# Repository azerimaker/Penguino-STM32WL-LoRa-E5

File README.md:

## Penguino-STM32WL-LoRa-E5
 Seeedstudio's [LoRa-E5 STM32WLE5JC](https://www.seeedstudio.com/LoRa-E5-Wireless-Module-p-4745.html) module was recently announced, and I took the liberty of designing a Penguino Feather breakout board for it. Hopefully OSHW community would benfit from it. 

## About the Penguino Feather breakout
Managed to fit everything on a +2 layer (H1.6mm) low-cost PCB. Careful design choices allowed to have a good GND plane on the back to to achieve good (theoretical) RF performance. 

_Current version: 0.1_

Board requirements are standard: 
- 6mil traces/clearance
- 0.3mm drill

### Specs (SoC): 
- [STM32WLE5JC](https://www.st.com/en/microcontrollers-microprocessors/stm32wle5jc.html) Wireless SoC
- ARM Cortex M4 ultra-low-power MCU
- Integrated SX1262 RF transciever
- Frequency range: 150 MHz to 960 MHz.
- Modulation: LoRa®, (G)FSK, (G)MSK and BPSK
- Transmitter power: programmable up to +22 dBm 

### Specs ([LoRa-E5 module](](https://www.seeedstudio.com/LoRa-E5-Wireless-Module-p-4745.html))): 
- Frequency range: EU868/US915/AU915/AS923/KR920/IN865 (high-band design). FCC and CE Certified
- Ultra-low Power Consumption: as low as 2.1uA sleep current (WOR mode)
- High Performance: TXOP=22dBm@868/915MHz; -136.5dBm sensitivity for SF12 with 125KHz BW 
- Long Distance Use: 158dB link budget
- Size: 12mm * 12mm * 2.5mm 28 pins SMT
- For further specs plese see the respective product pages. 

### License:
- Hardware license: CERN-OHL-S v2
- Software license: under MIT unless otherise indicated 
- Documentation license:  CC BY-SA 4.0 International.

## Open Source Hardware
This board is an OSHWA approved design: [AZ000003](https://certification.oshwa.org/az000003.html)

### Contact:
If you have any question or comments please feel free to open an issue (or a discussion or drop me a message at [@azerimaker](https://twitter.com/azerimaker).

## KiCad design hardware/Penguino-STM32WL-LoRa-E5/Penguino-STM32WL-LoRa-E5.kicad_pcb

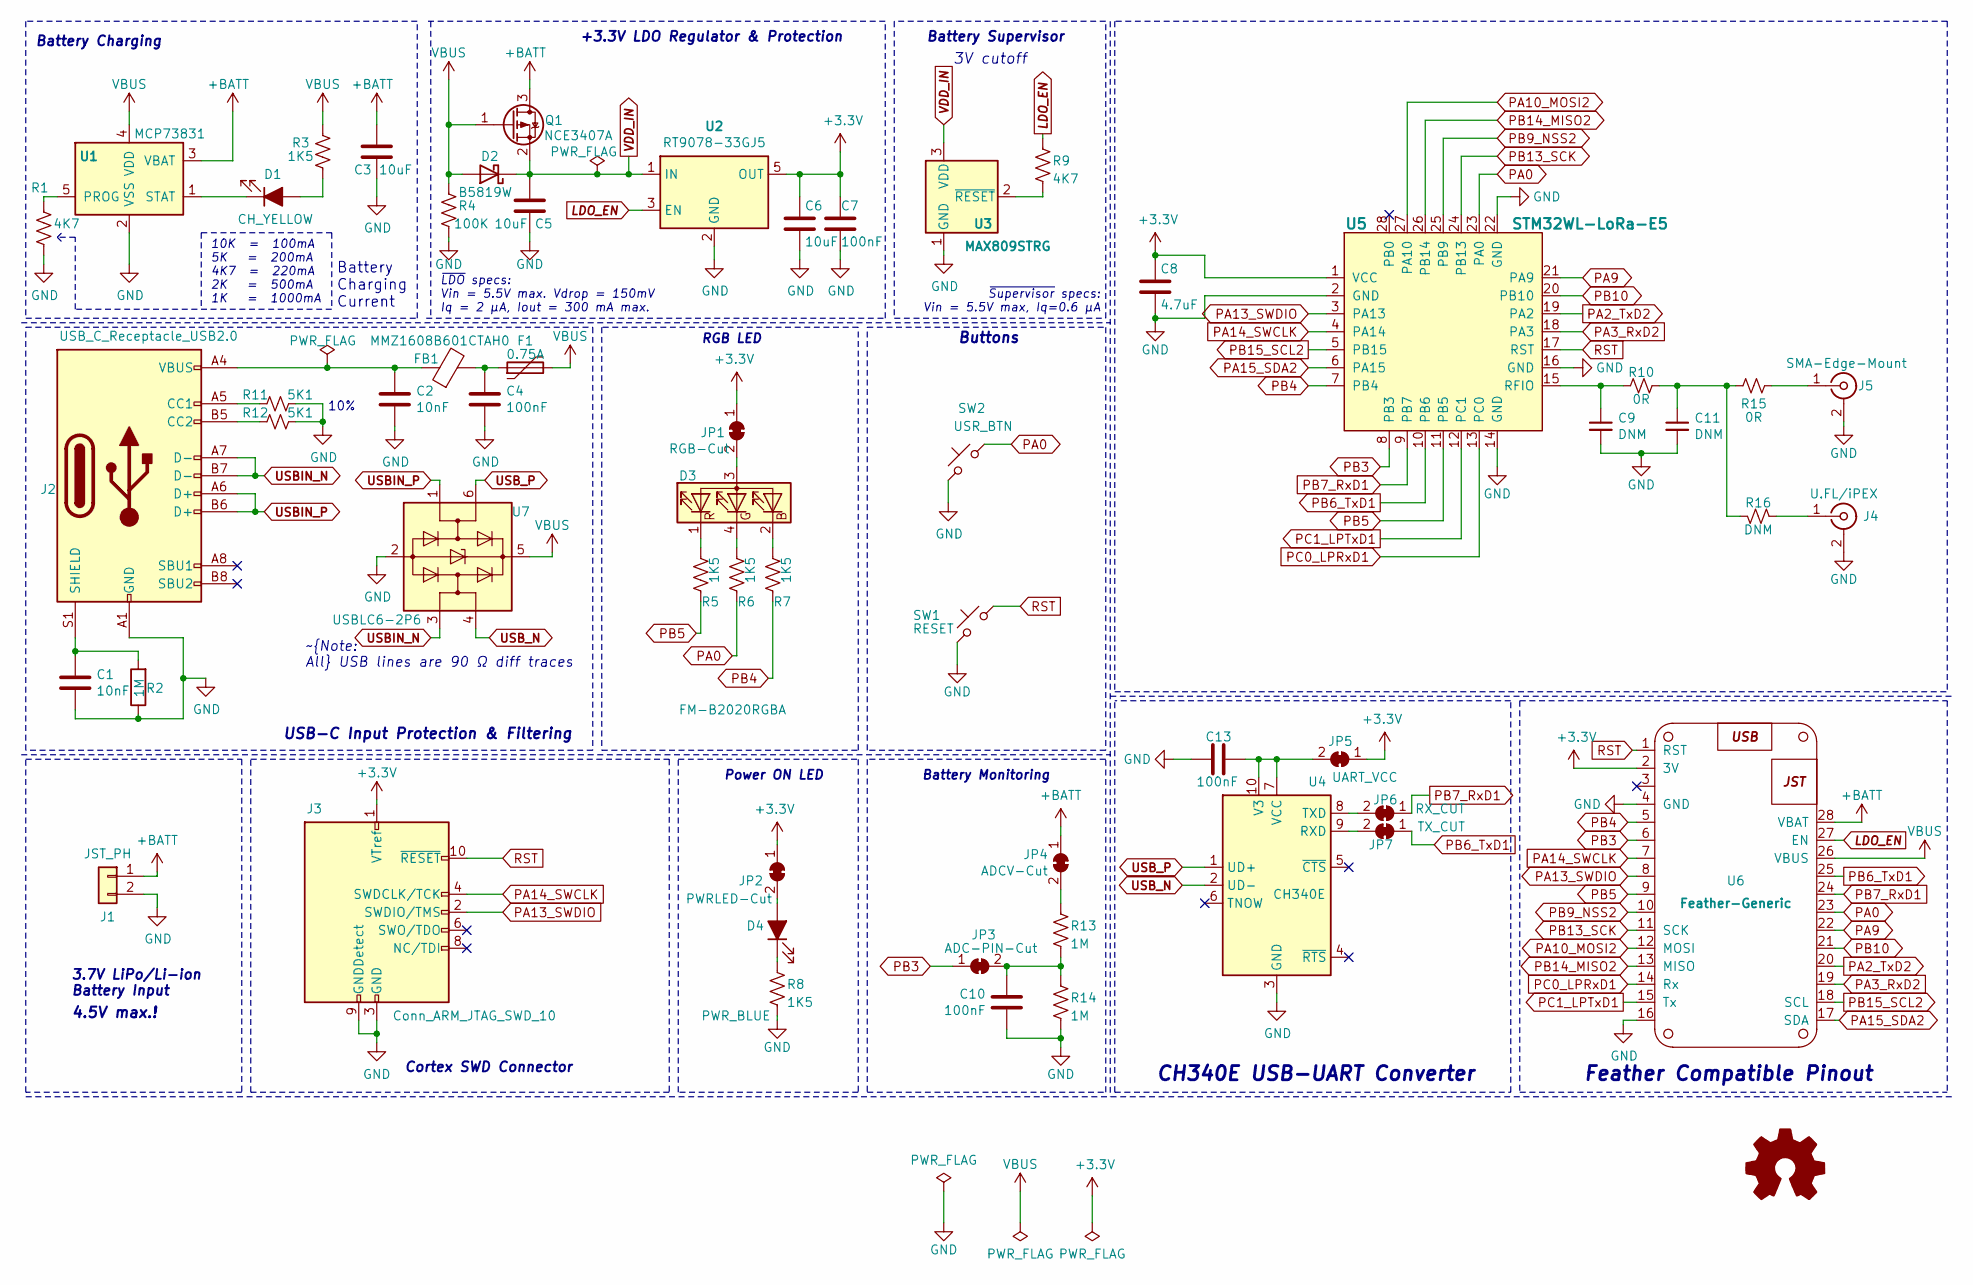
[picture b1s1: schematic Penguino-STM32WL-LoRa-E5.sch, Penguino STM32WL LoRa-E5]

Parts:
C1, C2: 10nF; C_0402_1005Metric; MPN CC0402KRX7R9BB103; LCSC_Part# C57112
C3, C5, C6: 10uF; C_0603_1608Metric; MPN CC0603KRX5R6BB106; LCSC_Part# C19702
C4, C7: 100nF; C_0402_1005Metric; MPN GRM155R61A104KA01D; LCSC_Part# C14663
C8: 4.7uF; C_0603_1608Metric; MPN CC0603KRX5R6BB475
C9, C11: DNM; C_0402_1005Metric; MPN DNM
C10, C13: 100nF; C_0402_1005Metric; MPN GRM155R61A104KA01D; LCSC_Part# C1525
D1: CH_YELLOW; LED_0603_1608Metric; MPN 19-217-Y5C-AM1N1VY-3T; LCSC_Part# C375450
D2: B5819W; D_SOD-123; MPN B5819W
D3: FM-B2020RGBA; LED_Cree-PLCC4_2x2mm_CW; MPN FM-B2020RGBA-HG; LCSC_Part# C108793
D4: PWR_BLUE; LED_0603_1608Metric; MPN 19-217-BHC-ZL1M2RY-3T; LCSC_Part# C72041
F1: 0.75A; Fuse_0805_2012Metric; MPN SMD0805P075TF; LCSC_Part# C20979
FB1: MMZ1608B601CTAH0; L_0603_1608Metric; MPN MMZ1608B601CTAH0; LCSC_Part# C98286
J1: JST_PH; JST_PH_S2B-PH-SM4-TB_1x02-1MP_P2.00mm_Horizontal; MPN S2B-PH-SM4-TB(LF)(SN)
J2: USB_C_Receptacle_USB2.0; USB_C_Receptacle_HRO_TYPE-C-31-M-12; MPN TYPE-C-31-M-12
J3: Conn_ARM_JTAG_SWD_10; PinHeader_2x05_P1.27mm_Vertical_SMD_noPaste; MPN 20021121-00010C4LF
J4: U.FL/iPEX; U.FL_Hirose_U.FL-R-SMT-1_Vertical; MPN U.FL-R-SMT-1(80)
J5: SMA-Edge-Mount; SMA_J_P_X_ST_EM1_EdgeMount; MPN DNM
JP1: RGB-Cut; SolderJumper-2_P1.3mm_Bridged_RoundedPad1.0x1.5mm; MPN DNM
JP2: PWRLED-Cut; SolderJumper-2_P1.3mm_Bridged_RoundedPad1.0x1.5mm; MPN DNM
JP3: ADC-PIN-Cut; SolderJumper-2_P1.3mm_Bridged_RoundedPad1.0x1.5mm; MPN DNM
JP4: ADCV-Cut; SolderJumper-2_P1.3mm_Bridged_RoundedPad1.0x1.5mm; MPN DNM
JP5: UART_VCC; SolderJumper-2_P1.3mm_Bridged_RoundedPad1.0x1.5mm; MPN DNM
JP6: RX_CUT; SolderJumper-2_P1.3mm_Bridged_RoundedPad1.0x1.5mm; MPN DNM
JP7: TX_CUT; SolderJumper-2_P1.3mm_Bridged_RoundedPad1.0x1.5mm; MPN DNM
Q1: NCE3407A; SOT-23; MPN NCE3407A; LCSC_Part# C2593
R1, R9: 4K7; R_0402_1005Metric; MPN RC0402JR-074K7L; LCSC_Part# C25900
R2, R13: 1M; R_0402_1005Metric; MPN RC0402JR-071ML; LCSC_Part# C26083
R3, R5, R6, R7, R8: 1K5; R_0402_1005Metric; MPN RC0402JR-071K5L; LCSC_Part# C25862
R4: 100K; R_0402_1005Metric; MPN RC0402JR-07100KL; LCSC_Part# C25741
R10, R15: 0R; R_0402_1005Metric; MPN RC0402JR-070RL
R11, R12: 5K1; R_0402_1005Metric; MPN RC0402FR-075K1L
R14: 1M; R_0402_1005Metric; MPN RC0402JR-071ML
R16: DNM; R_0402_1005Metric; MPN DNM
SW1: RESET; SW_Push_SKRPACE010; MPN SKRPACE010
SW2: USR_BTN; SW_Push_SKRPACE010; MPN SKRPACE010
U1: MCP73831; SOT-23-5; MPN MCP73831T-2ACI/OT; LCSC_Part# C424093
U2: RT9078-33GJ5; TSOT-23-5; MPN RT9078-33GJ5; LCSC_Part# C110427
U3: MAX809STRG; SOT-23; MPN MAX809STRG; LCSC_Part# C9965
U4: CH340E; MSOP-10_3x3mm_P0.5mm; MPN CH340E; LCSC_Part# C99652
U5: STM32WL-LoRa-E5; stm32wl-LoRa-E5-w-paste; MPN LoRa-E5-HF
U6: Feather-Generic
U7: USBLC6-2P6; SOT-666; MPN USBLC6-2P6

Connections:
+3V3: C6.1, C7.1, C8.1, J3.1 (VTref), JP1.1 (A), JP2.1 (A), JP5.1 (A), U2.5 (OUT), U5.1 (VCC), U6.2 (3V)
+BATT: C3.1, J1.1, JP4.1 (A), Q1.3 (D), U1.3 (VBAT), U6.28 (VBAT)
GND: C1.1, C2.2, C3.2, C4.2, C5.2, C6.2, C7.2, C8.2, C9.2, C10.1, C11.2, C13.2, J1.2, J2.A1 (GND), J2.A12 (GND), J2.B1 (GND), J2.B12 (GND), J3.3 (GND), J3.5 (GND), J3.9 (GNDDetect), J4.2 (Ext), J5.2 (Ext), R1.2, R2.1, R4.2, R8.2, R11.1, R12.1, R14.2, SW1.1, SW2.1, U1.2 (VSS), U2.2 (GND), U3.1 (GND), U4.3 (GND), U5.2 (GND), U5.14 (GND), U5.16 (GND), U5.22 (GND), U6.4 (GND), U6.16, U7.2 (GND)
LDO_EN: R9.1, U2.3 (EN), U6.27 (EN)
unnamed: C1.2, J2.S1 (SHIELD), R2.2
unnamed: C2.1, FB1.1, J2.A4 (VBUS), J2.A9 (VBUS), J2.B4 (VBUS), J2.B9 (VBUS)
unnamed: C4.1, F1.1, FB1.2
unnamed: C9.1, R10.2, U5.15 (RFIO)
unnamed: C10.2, JP3.2 (B), R13.2, R14.1
unnamed: C11.1, R10.1, R15.2, R16.1
unnamed: C13.1, JP5.2 (B), U4.7 (VCC), U4.10 (V3)
unnamed: D1.1 (K), U1.1 (STAT)
unnamed: D1.2 (A), R3.2
unnamed: D3.1 (RK), R5.1
unnamed: D3.2 (BK), R7.1
unnamed: D3.3 (A), JP1.2 (B)
unnamed: D3.4 (GK), R6.1
unnamed: D4.1 (K), R8.1
unnamed: D4.2 (A), JP2.2 (B)
unnamed: J2.A5 (CC1), R11.2
unnamed: J2.B5 (CC2), R12.2
unnamed: J4.1 (In), R16.2
unnamed: J5.1 (In), R15.1
unnamed: JP4.2 (B), R13.1
unnamed: JP6.2 (B), U4.8 (TXD)
unnamed: JP7.2 (B), U4.9 (RXD)
unnamed: R1.1, U1.5 (PROG)
unnamed: R9.2, U3.2 (~RESET)
PA0: R6.2, SW2.2, U5.23 (PA0), U6.23
PA2_TxD2: U5.19 (PA2), U6.20
PA3_RxD2: U5.18 (PA3), U6.19
PA9: U5.21 (PA9), U6.22
PA10_MOSI2: U5.27 (PA10), U6.12 (MOSI)
PA13_SWDIO: J3.2 (SWDIO/TMS), U5.3 (PA13), U6.8
PA14_SWCLK: J3.4 (SWDCLK/TCK), U5.4 (PA14), U6.7
PA15_SDA2: U5.6 (PA15), U6.17 (SDA)
PB3: JP3.1 (A), U5.8 (PB3), U6.6
PB4: R7.2, U5.7 (PB4), U6.5
PB5: R5.2, U5.11 (PB5), U6.9
PB6_TxD1: JP7.1 (A), U5.10 (PB6), U6.25
PB7_RxD1: JP6.1 (A), U5.9 (PB7), U6.24
PB9_NSS2: U5.25 (PB9), U6.10
PB10: U5.20 (PB10), U6.21
PB13_SCK: U5.24 (PB13), U6.11 (SCK)
PB14_MISO2: U5.26 (PB14), U6.13 (MISO)
PB15_SCL2: U5.5 (PB15), U6.18 (SCL)
PC0_LPRxD1: U5.13 (PC0), U6.14 (Rx)
PC1_LPTxD1: U5.12 (PC1), U6.15 (Tx)
RST: J3.10 (~RESET~), SW1.2, U5.17 (RST), U6.1 (RST)
USBIN_N: J2.A7 (D-), J2.B7 (D-), U7.3 (I/O2)
USBIN_P: J2.A6 (D+), J2.B6 (D+), U7.1 (I/O1)
USB_N: U4.2 (UD-), U7.4 (I/O2)
USB_P: U4.1 (UD+), U7.6 (I/O1)
VBUS: D2.2 (A), F1.2, Q1.1 (G), R3.1, R4.1, U1.4 (VDD), U6.26 (VBUS), U7.5 (VBUS)
VDD_IN: C5.1, D2.1 (K), Q1.2 (S), U2.1 (IN), U3.3 (VDD)

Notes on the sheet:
10K = 100mA 5K = 200mA 4K7 = 220mA 2K = 500mA 1K = 1000mA
3.7V LiPo/Li-ion Battery Input
Battery Charging
USB-C Input Protection & Filtering
RGB LED
Battery Monitoring
Cortex SWD Connector
~Note: All USB lines are 90 Ω diff traces
Buttons
+3.3V LDO Regulator & Protection
Battery Supervisor
~LDO specs: Vin = 5.5V max. Vdrop = 150mV Iq = 2 μA, Iout = 300 mA max.
3V cutoff
~Supervisor specs: Vin = 5.5V max, Iq=0.6 μA
4.5V max.!
Feather Compatible Pinout
Power ON LED
CH340E USB-UART Converter
Battery Charging Current
10%

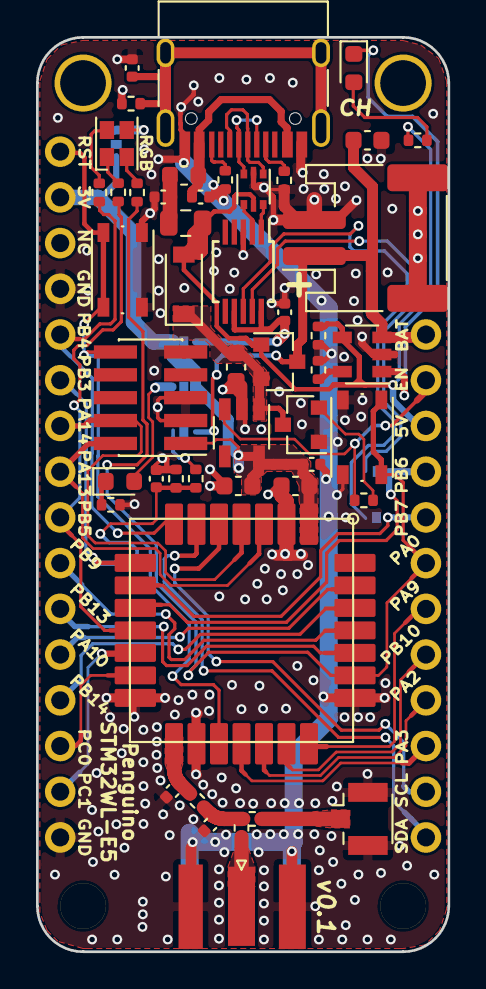
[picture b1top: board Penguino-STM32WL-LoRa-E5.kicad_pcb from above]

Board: 2 copper layers, 22.9 x 50.8 mm, 57 parts (0 on the bottom side), 55 nets.

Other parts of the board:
G-Penguino: LOGO; Penguino-SM-5500

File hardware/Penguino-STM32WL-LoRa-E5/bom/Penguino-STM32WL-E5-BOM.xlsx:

Item | Qty | Reference(s) | MPN | MPN_ALT | Seeed SKU | Value | Footprint | URL
1 | 2 | C1, C2 | CC0402KRX7R9BB103 | ~ | 302010006 | 10nF | Capacitor_SMD:C_0402_1005Metric | https://lcsc.com/product-detail/Multilayer-Ceramic-Capacitor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
2 | 3 | C3, C5, C6 | CC0603KRX5R6BB106 | ~ | 302010103 | 10uF | Capacitor_SMD:C_0603_1608Metric | https://lcsc.com/product-detail/Others_YAGEO-CC0603KRX5R6BB1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
3 | 4 | C4, C7, C10, C13 | GRM155R61A104KA01D | ~ | 302010037 | 100nF | Capacitor_SMD:C_0402_1005Metric | https://lcsc.com/product-detail/Multilayer-Ceramic-Capacitor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
4 | 1 | C8 | CC0603KRX5R6BB475 | ~ | 302010111 | 4.7uF | Capacitor_SMD:C_0603_1608Metric | https://lcsc.com/product-detail/Multilayer-Ceramic-Capacitor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
5 | 0 | C9, C11 | DNM | ~ |  | DNM | Capacitor_SMD:C_0402_1005Metric | ~
6 | 1 | D1 | 19-217-Y5C-AM1N1VY-3T | ~ | 304090044 | CH_YELLOW | LED_SMD:LED_0603_1608Metric | https://lcsc.com/product-detail/Others_Everlight-Elec-19-217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
7 | 1 | D2 | B5819W | ~ | 304020034 | B5819W | Diode_SMD:D_SOD-123 | https://lcsc.com/product-detail/Schottky-Barrier-Diodes-SBD_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
8 | 1 | D3 | FM-B2020RGBA-HG | ~ | ~ | FM-B2020RGBA RGB LED | LED_SMD:LED_Cree-PLCC4_2x2mm_CW | https://lcsc.com/product-detail/Light-Emitting-Diodes-LED_Fo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
9 | 1 | D4 | 19-217-BHC-ZL1M2RY-3T | ~ | 304090045 | PWR_BLUE | LED_SMD:LED_0603_1608Metric | https://lcsc.com/product-detail/Light-Emitting-Diodes-LED_06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
10 | 1 | F1 | SMD0805P075TF | ~ | ~ | 0.75A | Fuse:Fuse_0805_2012Metric | https://lcsc.com/product-detail/PTC-Resettable-Fuses_PTTC-Po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
11 | 1 | FB1 | MMZ1608B601CTAH0 | ~ | ~ | MMZ1608B601CTAH0 | Inductor_SMD:L_0603_1608Metric | https://lcsc.com/product-detail/Ferrite-Beads_TDK-MMZ1608B60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
12 | 1 | J1 | S2B-PH-SM4-TB(LF)(SN) | ~ | ~ | JST_PH | Connector_JST:JST_PH_S2B-PH-SM4-TB_1x02-1MP_P2.00mm_Horizontal | https://lcsc.com/product-detail/Wire-To-Board-Wire-To-Wire-C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
13 | 1 | J2 | TYPE-C-31-M-12 | ~ | ~ | USB_C_Receptacle_USB2.0 | Connector_USB:USB_C_Receptacle_Palconn_UTC16-G | https://lcsc.com/product-detail/USB-Connectors_Korean-Hropar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
14 | 1 | J3 | 20021121-00010C4LF | ~ | ~ | Conn_ARM_JTAG_SWD_10 | penguino_v1:PinHeader_2x05_P1.27mm_Vertical_SMD_noPaste | https://lcsc.com/product-detail/Pin-Header-Female-Header_Amp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
15 | 1 | J4 | U.FL-R-SMT-1(10) | ~ | 320111077 | U.FL/iPEX | Connector_Coaxial:U.FL_Hirose_U.FL-R-SMT-1_Vertical | https://lcsc.com/product-detail/RF-Connectors-Coaxial-Connec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
16 | 1 | J5 | BWSMA-KE-P001 | ~ | ~ | SMA-Edge-Mount | penguino_v1:SMA_J_P_X_ST_EM1_EdgeMount | https://lcsc.com/product-detail/RF-Connectors-Coaxial-Connec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
17 | 0 | JP1 | DNM | ~ | ~ | RGB-Cut | Jumper:SolderJumper-2_P1.3mm_Bridged_RoundedPad1.0x1.5mm | ~
18 | 0 | JP2 | DNM | ~ | ~ | PWRLED-Cut | Jumper:SolderJumper-2_P1.3mm_Bridged_RoundedPad1.0x1.5mm | ~
19 | 0 | JP3 | DNM | ~ | ~ | ADC-PIN-Cut | Jumper:SolderJumper-2_P1.3mm_Bridged_RoundedPad1.0x1.5mm | ~
20 | 0 | JP4 | DNM | ~ | ~ | ADCV-Cut | Jumper:SolderJumper-2_P1.3mm_Bridged_RoundedPad1.0x1.5mm | ~
21 | 0 | JP5 | DNM | ~ | ~ | UART_VCC | Jumper:SolderJumper-2_P1.3mm_Bridged_RoundedPad1.0x1.5mm | ~
22 | 0 | JP6 | DNM | ~ | ~ | RX_CUT | Jumper:SolderJumper-2_P1.3mm_Bridged_RoundedPad1.0x1.5mm | ~
23 | 0 | JP7 | DNM | ~ | ~ | TX_CUT | Jumper:SolderJumper-2_P1.3mm_Bridged_RoundedPad1.0x1.5mm | ~
24 | 1 | Q1 | NCE3407A | ~ | 305030010 | NCE3407A | Package_TO_SOT_SMD:SOT-23 | https://lcsc.com/product-detail/MOSFET_Wuxi-NCE-Power-Semico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
25 | 2 | R1, R9 | RC0402JR-074K7L | ~ | 301010010 | 4K7 | Resistor_SMD:R_0402_1005Metric | https://lcsc.com/product-detail/Chip-Resistor-Surface-Mount_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
26 | 3 | R2, R13, R14 | RC0402JR-071ML | ~ | 301010009 | 1M | Resistor_SMD:R_0402_1005Metric | https://lcsc.com/product-detail/Chip-Resistor-Surface-Mount_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
27 | 5 | R3, R5, R6, R7, R8 | RC0402JR-071K5L | ~ | 301010001 | 1K5 | Resistor_SMD:R_0402_1005Metric | https://lcsc.com/product-detail/Chip-Resistor-Surface-Mount_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
28 | 1 | R4 | RC0402JR-07100KL | ~ | 301010033 | 100K | Resistor_SMD:R_0402_1005Metric | https://lcsc.com/product-detail/Chip-Resistor-Surface-Mount_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
29 | 2 | R10, R15 | RC0402JR-070RL | ~ | 301010000 | 0R | Resistor_SMD:R_0402_1005Metric | https://lcsc.com/product-detail/Chip-Resistor-Surface-Mount_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
30 | 2 | R11, R12 | RC0402FR-075K1L | ~ | 301010495 | 5K1 | Resistor_SMD:R_0402_1005Metric | https://lcsc.com/product-detail/Chip-Resistor-Surface-Mount_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
31 | 0 | R16 | DNM | ~ | ~ | DNM | Resistor_SMD:R_0402_1005Metric | ~
32 | 2 | SW1, SW2 | SKRPACE010 | ~ | ~ | RESE, USR_BTN | penguino_v1:SW_Push_SKRPACE010 | https://lcsc.com/product-detail/Tactile-Switches_ALPS-Electr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
33 | 1 | U1 | MCP73831T-2ACI/OT | ~ | ~ | MCP73831 | Package_TO_SOT_SMD:SOT-23-5 | https://lcsc.com/product-detail/PMIC-Battery-Management_Micr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
34 | 1 | U2 | RT9078-33GJ5 | ~ | ~ | RT9078-33GJ5 | Package_TO_SOT_SMD:TSOT-23-5 | https://lcsc.com/product-detail/Dropout-Regulators-LDO_Richt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
35 | 1 | U3 | MAX809STRG | ~ | ~ | MAX809STRG | Package_TO_SOT_SMD:SOT-23 | https://lcsc.com/product-detail/Microprocessor-Microcontroll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
36 | 1 | U4 | CH340E | ~ | ~ | CH340E | Package_SO:MSOP-10_3x3mm_P0.5mm | https://lcsc.com/product-detail/USB-ICs_WCH-Jiangsu-Qin-Heng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
37 | 1 | U5 | LoRa-E5-HF | ~ | ~ | STM32WL-LoRa-E5 | stm32wl-lib-v1:stm32wl-LoRa-E5-w-paste | https://www.seeedstudio.com/LoRa-E5-Wireless-Module-p-4745.html
38 | 1 | U7 | USBLC6-2P6 | ~ | ~ | USBLC6-2P6 | Package_TO_SOT_SMD:SOT-666 | https://lcsc.com/product-detail/Diodes-ESD_STMicroelectronic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
Date: | 12/1/2020 7:00:41 PM
Tool: | Eeschema (5.1.8)-1
Component Count: | 45
Individual Components: | 38

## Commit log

2020-12-02 Readme update, rev01 design files
2020-12-02 Readme update
2020-12-02 Readme fix (one of many)
2020-12-20 fix: NRST and USB Footprint
2020-12-20 fix: PDF Schematics
2020-12-21 fix: Gerber update
2021-03-24 add: RGB toggle example
2021-03-25 doc: OSHW license and UID added
2021-04-09 doc: Add iBOM file
2021-05-30 Update example
